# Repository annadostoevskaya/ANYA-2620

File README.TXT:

ANYA-2620 / A2027

Авторы: Kanat M. M. и Anna D. A.
Текущая версия платы: V2I1. Среда разработки: KiCad.

С чего начать

Открыть проект: hardware/v2i1/A2027.kicad_pro
Открыть схему:  hardware/v2i1/A2027.kicad_sch
Открыть плату:  hardware/v2i1/A2027.kicad_pcb
Посмотреть BOM: manufacturing/v2i1/bom/Bill_Of_Materials.csv
Посмотреть CPL: manufacturing/v2i1/cpl/Component_Placement_List.csv

Артикулы производителей, поставщики, ссылки на товары и Datasheet
хранятся в полях компонентов схемы. Для выгрузки BOM в редакторе схемы:
Tools → Generate Bill of Materials… → preset Purchasing BOM →
format Purchasing CSV → Export. Путь вывода уже настроен.
Preset Purchasing BOM - fitted only исключает DNP (C1,C6,C18).
Редактировать закупочные данные через Tools → Edit Symbol Fields…

Структура

hardware/
  v2i1/               Текущие исходники KiCad: проект, схема и плата.
    libs/              Локальная библиотека символов.
    3dmodels/          Локальные 3D-модели.
    .history/          Сохранённая история KiCad; отдельный вложенный Git-репозиторий.

firmware/
  Firmware.ioc         Конфигурация STM32CubeMX. Исходников прошивки пока нет.

manufacturing/
  v2i1/
    gerbers/           Gerber, сверловка и A2027-job.gbrjob в одной папке.
    bom/               Экспортированный BOM текущей платы.
    cpl/               Позиции 81 устанавливаемого компонента; X/Y в mm,
                       верхняя сторона top, поворот в градусах 0–360.
                       Координаты KiCad без сдвига начала; DNP, отверстия
                       и паяная перемычка исключены. Включены 5 THT-разъёмов.

docs/
  design/              Блок-схема Excalidraw и расчёты Mathcad.
  references/          Справочные материалы и схемы отладочных плат.
  reviews/             Отчёты ревью платы.

archive/
  v1i1/source/         Предыдущая версия платы в Altium.
  v1i1/release-template/ Старый шаблон выпуска V1I1 с инструкциями.
  altium/              Старые библиотеки, 3D-модели и правила Altium.
  footprint-expert-2025/ Исходные материалы Footprint Expert.
  project-template/    Исходный README и прежние шаблонные инструкции.
  local-state/         Сохранённые служебные файлы Finder из старых каталогов.

Как поддерживать порядок

Редактировать текущую электронику в hardware/v2i1/.
Файлы *.kicad_pro, *.kicad_sch и *.kicad_pcb оставлять с одним именем A2027.
При изменении версии создавать новые каталоги с номером версии.
Экспортировать Gerber в manufacturing/v2i1/gerbers/, BOM — в manufacturing/v2i1/bom/.
Настройки вывода KiCad обновлены на эти пути. Локальные библиотеки и модели
используют ${KIPRJMOD} и перемещены вместе с проектом.

Gerber — существовавший экспорт от 2026-11-03; при реорганизации
они не пересоздавались. BOM и CPL сгенерированы из текущих исходников.
Перед отправкой в производство
проверять их соответствие текущим исходникам и фиксировать утверждённый выпуск.
Рабочие изменения сохранять в Git основного проекта. Вложенная .history
сохранена как была и не заменяет историю основного репозитория.

Реорганизация каталогов: 2026-11-03. Содержимое прежних файлов сохранено,
кроме настроек путей экспорта KiCad и ссылок на библиотеки старого Altium.

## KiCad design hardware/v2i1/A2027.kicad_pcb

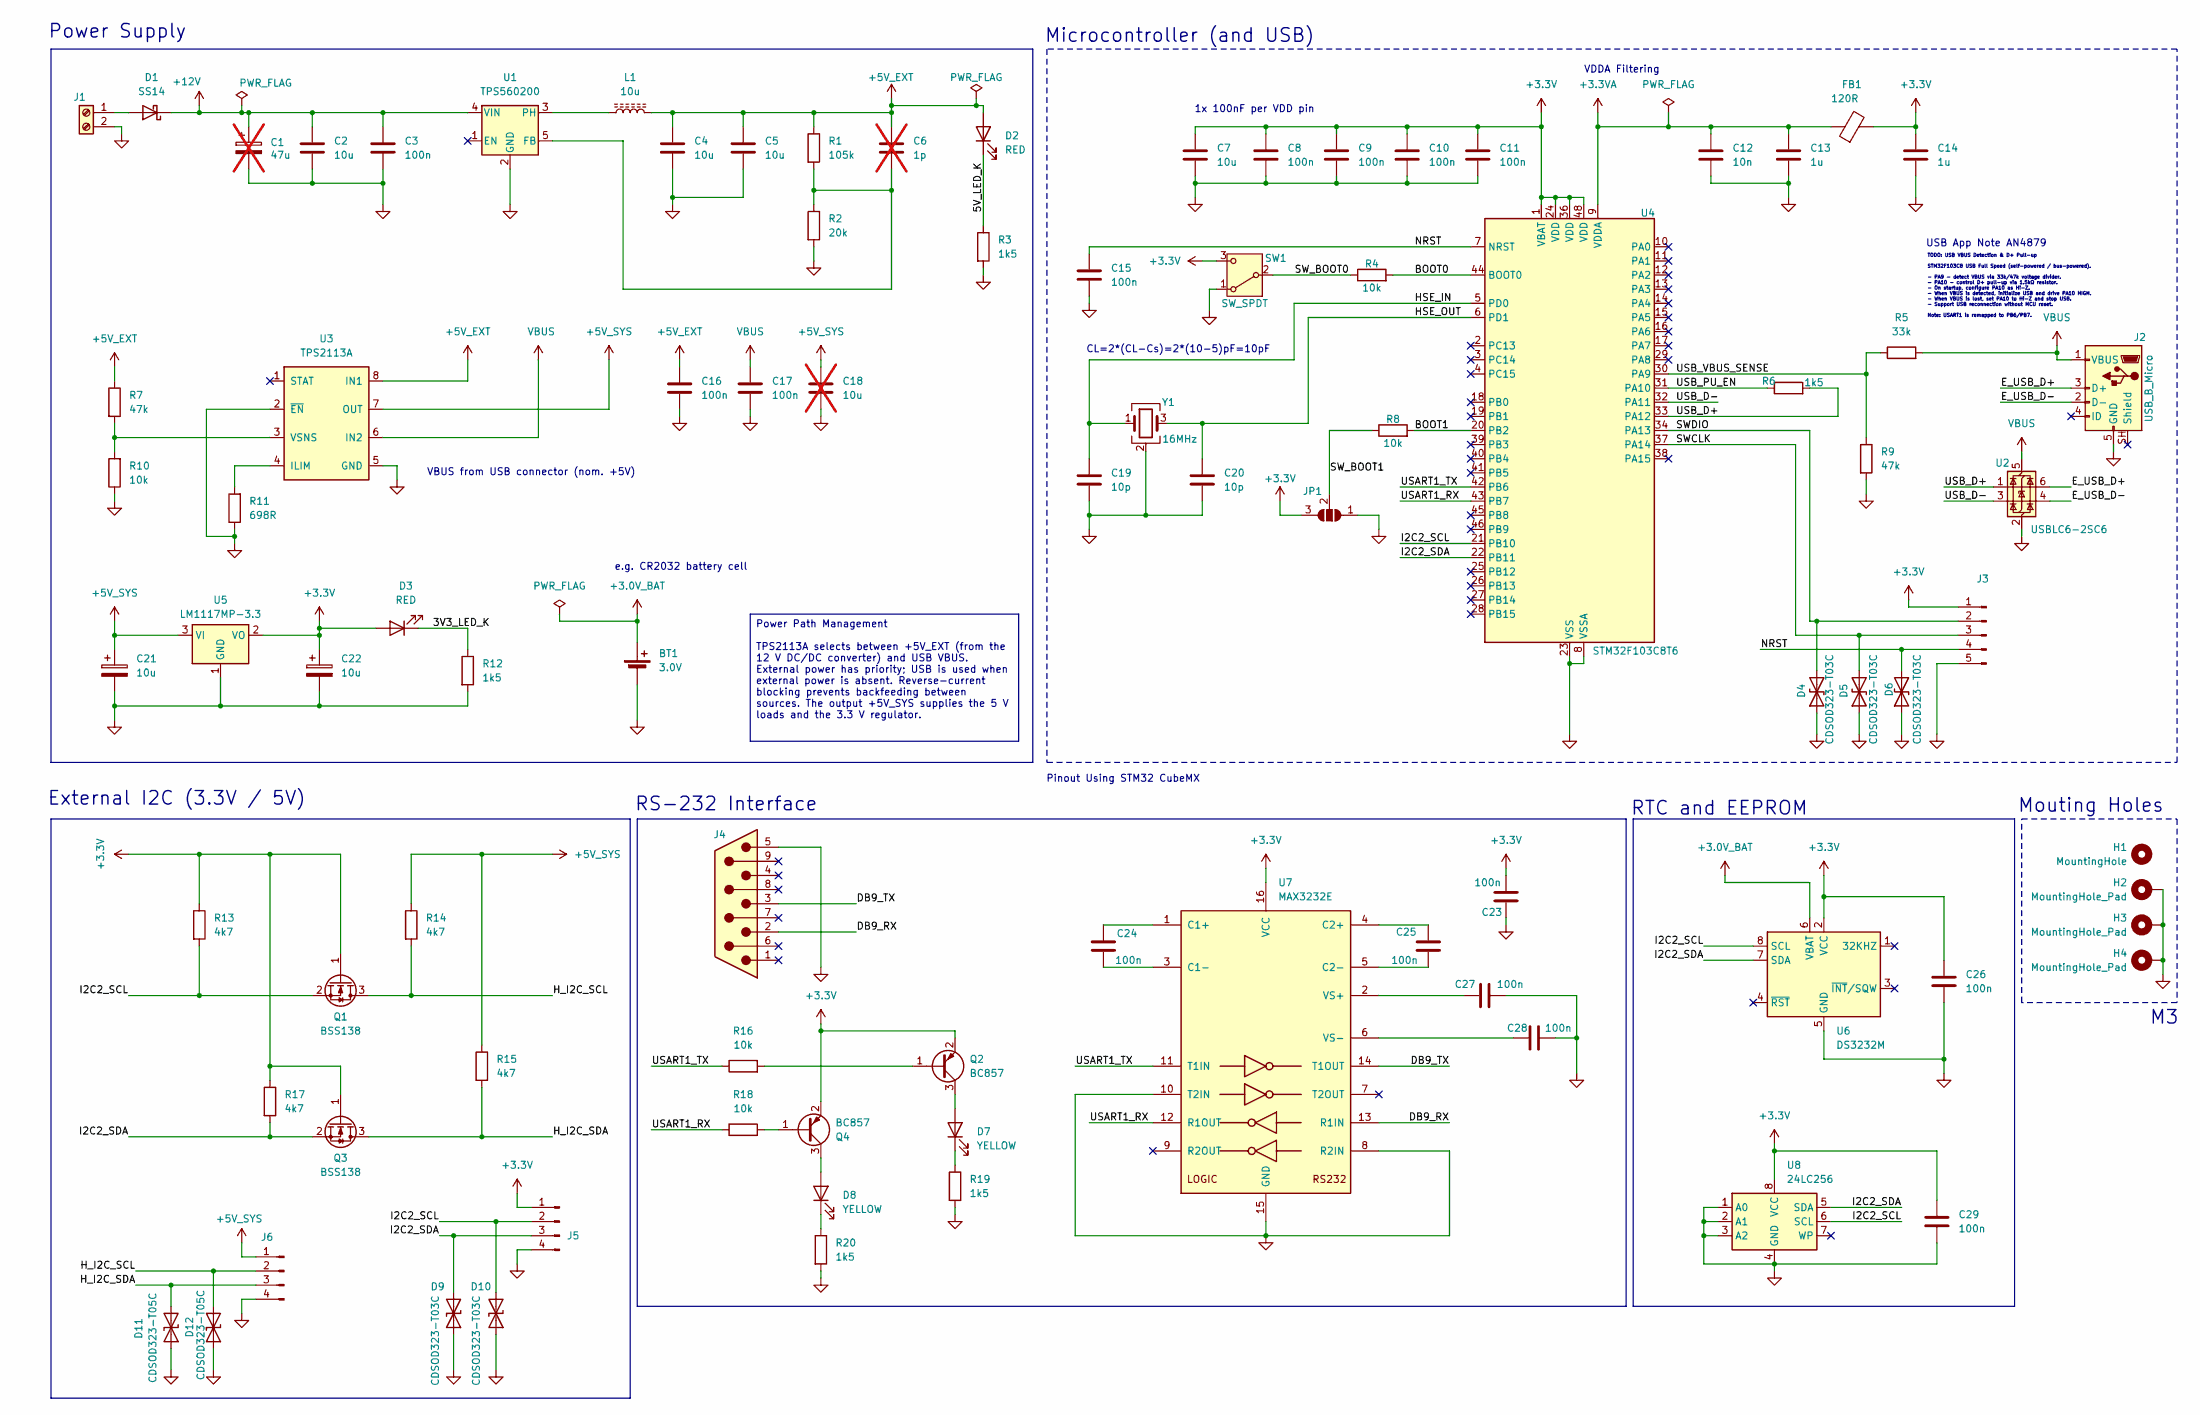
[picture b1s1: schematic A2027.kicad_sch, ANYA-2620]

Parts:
BT1: 3.0V; BatteryHolder_Keystone_3034_1x20mm; Manufacturer_Part_Number 3034
C1: 47u; CP_Elec_6.3x5.8; not fitted
C2, C4, C5: 10u; C_1210_3225Metric; Manufacturer_Part_Number CL32B106KBJNNNE
C3, C8, C9, C10, C11, C15, C16, C17, C23, C24, C25, C26, C27, C28, C29: 100n; C_0402_1005Metric; Manufacturer_Part_Number CL05B104KB5NNNC
C6: 1p; C_0402_1005Metric; not fitted
C7: 10u; C_0603_1608Metric; Manufacturer_Part_Number CL10B106MQ8NRNC
C12: 10n; C_0402_1005Metric; Manufacturer_Part_Number CL05B103KB5NNNC
C13, C14: 1u; C_0402_1005Metric; Manufacturer_Part_Number GRM155R70J105KA12D
C18: 10u; C_0603_1608Metric; not fitted
C19, C20: 10p; C_0402_1005Metric; Manufacturer_Part_Number GRM1555C1H100JA01D
C21, C22: 10u; CP_EIA-3216-18_Kemet-A; Manufacturer_Part_Number TAJA106K016RNJ
D1: SS14; D_SMA; Manufacturer_Part_Number SS14
D2, D3: RED; LED_0603_1608Metric; Manufacturer_Part_Number KT-0603R
D4, D5, D6, D9, D10: CDSOD323-T03C; D_SOD-323; Manufacturer_Part_Number CDSOD323-T03C
D7, D8: YELLOW; LED_0603_1608Metric; Manufacturer_Part_Number KT-0603Y
D11, D12: CDSOD323-T05C; D_SOD-323; Manufacturer_Part_Number CDSOD323-T05C
FB1: 120R; L_0603_1608Metric; Manufacturer_Part_Number BLM18PG121SN1D
H1: MountingHole; MountingHole_3.2mm_M3
H2, H3, H4: MountingHole_Pad; MountingHole_3.2mm_M3_Pad_TopBottom
J1: Screw_Terminal_01x02; TerminalBlock_Phoenix_MKDS-1,5-2-5.08_1x02_P5.08mm_Horizont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; Manufacturer_Part_Number 1715721
J2: USB_B_Micro; USB_Micro-B_Wuerth_629105150521; Manufacturer_Part_Number 629105150521
J3: Conn_01x05_Pin; PinHeader_1x05_P2.54mm_Vertical; Manufacturer_Part_Number PZ254V-11-05P
J4: DS1037-09MNAKT74-0CC; DSUB-9_Pins_Horizontal_P2.77x2.84mm_EdgePinOffset7.70mm_Hou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; Manufacturer_Part_Number DS1037-09MNAKT74-0CC
J5, J6: Conn_01x04_Pin; PinHeader_1x04_P2.54mm_Vertical; Manufacturer_Part_Number PZ254V-11-04P
JP1: SolderJumper_3_Open; SolderJumper-3_P2.0mm_Open_TrianglePad1.0x1.5mm
L1: 10u; L_Bourns_SRP5030T; Manufacturer_Part_Number SRP5030T-100M
Q1, Q3: BSS138; SOT-23; Manufacturer_Part_Number BSS138LT1G
Q2, Q4: BC857; SOT-23; Manufacturer_Part_Number BC857BLT1G
R1: 105k; R_0402_1005Metric; Manufacturer_Part_Number 0402WGF1053TCE
R2: 20k; R_0402_1005Metric; Manufacturer_Part_Number 0402WGF2002TCE
R3, R12, R19, R20: 1k5; R_0402_1005Metric; Manufacturer_Part_Number 0402WGF1501TCE
R4, R8, R10, R16, R18: 10k; R_0402_1005Metric; Manufacturer_Part_Number 0402WGF1002TCE
R5: 33k; R_0402_1005Metric; Manufacturer_Part_Number 0402WGF3302TCE
R6: 1k5; R_0603_1608Metric; Manufacturer_Part_Number 0603WAF1501T5E
R7, R9: 47k; R_0402_1005Metric; Manufacturer_Part_Number 0402WGF4702TCE
R11: 698R; R_0402_1005Metric; Manufacturer_Part_Number 0402WGF6980TCE
R13, R14, R15, R17: 4k7; R_0402_1005Metric; Manufacturer_Part_Number 0402WGF4701TCE
SW1: SW_SPDT; SW_SPDT_PCM12; Manufacturer_Part_Number PCM12SMTR
U1: TPS560200; SOT-23-5; Manufacturer_Part_Number TPS560200DBVR
U2: USBLC6-2SC6; SOT-23-6; Manufacturer_Part_Number USBLC6-2SC6
U3: TPS2113A; TSSOP-8_4.4x3mm_P0.65mm; Manufacturer_Part_Number TPS2113APWR
U4: STM32F103C8T6; LQFP-48_7x7mm_P0.5mm; Manufacturer_Part_Number STM32F103C8T6
U5: LM1117MP-3.3; SOT-223-3_TabPin2; Manufacturer_Part_Number LM1117MP-3.3/NOPB
U6: DS3232M; SOIC-8_3.9x4.9mm_P1.27mm; Manufacturer_Part_Number DS3232MZ+
U7: MAX3232E; TSSOP-16_4.4x5mm_P0.65mm; Manufacturer_Part_Number MAX3232EIPWR
U8: 24LC256; SOIC-8_3.9x4.9mm_P1.27mm; Manufacturer_Part_Number 24LC256T-I/SN
Y1: 16MHz; Crystal_SMD_3225-4Pin_3.2x2.5mm; Manufacturer_Part_Number X322516MMB4SI

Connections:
+3.0V_BAT: BT1.1 (+), U6.6 (VBAT)
+3.3V: C7.1, C8.1, C9.1, C10.1, C11.1, C14.1, C22.1, C23.2, C26.1, C29.1, D3.2 (A), FB1.2, J3.1, J5.1, JP1.3 (B), Q1.1 (G), Q2.2 (E), Q3.1 (G), Q4.2 (E), R13.1, R17.1, SW1.3 (C), U4.1 (VBAT), U4.24 (VDD), U4.36 (VDD), U4.48 (VDD), U5.2 (VO), U6.2 (VCC), U7.16 (VCC), U8.8 (VCC)
+3.3VA: C12.1, C13.1, FB1.1, U4.9 (VDDA)
+5V_EXT: C4.1, C5.1, C6.1, C16.1, D2.2 (A), L1.2, R1.1, R7.1, U3.8 (IN1)
+5V_SYS: C18.1, C21.1, J6.1, R14.1, R15.1, U3.7 (OUT), U5.3 (VI)
+12V: C1.1, C2.1, C3.1, D1.1 (K), U1.4 (VIN)
/3V3_LED_K: D3.1 (K), R12.1
/5V_LED_K: D2.1 (K), R3.1
/BOOT0: R4.2, U4.44 (BOOT0)
/BOOT1: R8.2, U4.20 (PB2)
/DB9_RX: J4.2, U7.13 (R1IN)
/DB9_TX: J4.3, U7.14 (T1OUT)
/E_USB_D+: J2.3 (D+), U2.6 (I/O1)
/E_USB_D-: J2.2 (D-), U2.4 (I/O2)
/HSE_IN: C19.1, U4.5 (PD0), Y1.1
/HSE_OUT: C20.1, U4.6 (PD1), Y1.3
/H_I2C_SCL: D12.2 (A2), J6.2, Q1.3 (D), R14.2
/H_I2C_SDA: D11.2 (A2), J6.3, Q3.3 (D), R15.2
/I2C2_SCL: D10.2 (A2), J5.2, Q1.2 (S), R13.2, U4.21 (PB10), U6.8 (SCL), U8.6 (SCL)
/I2C2_SDA: D9.2 (A2), J5.3, Q3.2 (S), R17.2, U4.22 (PB11), U6.7 (SDA), U8.5 (SDA)
/NRST: C15.1, D6.2 (A2), J3.4, U4.7 (NRST)
/SWCLK: D5.2 (A2), J3.3, U4.37 (PA14)
/SWDIO: D4.2 (A2), J3.2, U4.34 (PA13)
/SW_BOOT0: R4.1, SW1.2 (B)
/SW_BOOT1: JP1.2 (C), R8.1
/USART1_RX: R18.1, U4.43 (PB7), U7.12 (R1OUT)
/USART1_TX: R16.1, U4.42 (PB6), U7.11 (T1IN)
/USB_D+: R6.2, U2.1 (I/O1), U4.33 (PA12)
/USB_D-: U2.3 (I/O2), U4.32 (PA11)
/USB_PU_EN: R6.1, U4.31 (PA10)
/USB_VBUS_SENSE: R5.1, R9.1, U4.30 (PA9)
GND: BT1.2 (-), C1.2, C2.2, C3.2, C4.2, C5.2, C7.2, C8.2, C9.2, C10.2, C11.2, C12.2, C13.2, C14.2, C15.2, C16.2, C17.2, C18.2, C19.2, C20.2, C21.2, C22.2, C23.1, C26.2, C27.2, C28.2, C29.2, D4.1 (A1), D5.1 (A1), D6.1 (A1), D9.1 (A1), D10.1 (A1), D11.1 (A1), D12.1 (A1), H2.1 (1_1), H3.1 (1_1), H4.1 (1_1), J1.2, J2.5 (GND), J3.5, J4.5, J5.4, J6.4, JP1.1 (A), R2.2, R3.2, R9.2, R10.1, R11.1, R12.2, R19.2, R20.2, SW1.1 (A), U1.2 (GND), U2.2 (GND), U3.2 (~EN), U3.5 (GND), U4.8 (VSSA), U4.23 (VSS), U4.35 (VSS), U4.47 (VSS), U5.1 (GND), U6.5 (GND), U7.8 (R2IN), U7.10 (T2IN), U7.15 (GND), U8.1 (A0), U8.2 (A1), U8.3 (A2), U8.4 (GND), Y1.2 (G), Y1.4 (G)
unnamed: D1.2 (A), J1.1
unnamed: D7.2 (A), Q2.3 (C)
unnamed: D7.1 (K), R19.1
unnamed: D8.2 (A), Q4.3 (C)
unnamed: D8.1 (K), R20.1
unnamed: Q2.1 (B), R16.2
unnamed: Q4.1 (B), R18.2
unnamed: C6.2, R1.2, R2.1, U1.5 (FB)
unnamed: L1.1, U1.3 (PH)
unnamed: R11.2, U3.4 (ILIM)
unnamed: R7.2, R10.2, U3.3 (VSNS)
unnamed: C24.1, U7.1 (C1+)
unnamed: C24.2, U7.3 (C1-)
unnamed: C25.1, U7.4 (C2+)
unnamed: C25.2, U7.5 (C2-)
unnamed: C27.1, U7.2 (VS+)
unnamed: C28.1, U7.6 (VS-)
VBUS: C17.1, J2.1 (VBUS), R5.2, U2.5 (VBUS), U3.6 (IN2)

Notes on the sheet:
TODO: USB VBUS Detection & D+ Pull-up STM32F103C8 USB Full Speed (self-powered / bus-powered). - PA9 - detect VBUS via 33k/47k voltage divider. - PA10 - control D+ pull-up via 1.5kΩ resistor. - On startup, configure PA10 as Hi-Z. - When VBUS is detected, initialize USB and drive PA10 HIGH. - When V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
RTC and EEPROM
Mouting Holes
Power Supply
External I2C (3.3V / 5V)
VBUS from USB connector (nom. +5V)
VDDA Filtering
RS-232 Interface
Microcontroller (and USB)
CL=2*(CL-Cs)=2*(10-5)pF=10pF
Pinout Using STM32 CubeMX
USB App Note AN4879
1x 100nF per VDD pin
e.g. CR2032 battery cell
Power Path Management TPS2113A selects between +5V_EXT (from the 12 V DC/DC converter) and USB VBUS. External power has priority; USB is used when external power is absent. Reverse-current blocking prevents backfeeding between sources. The output +5V_SYS supplies the 5 V loads and the 3.3 V regulat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

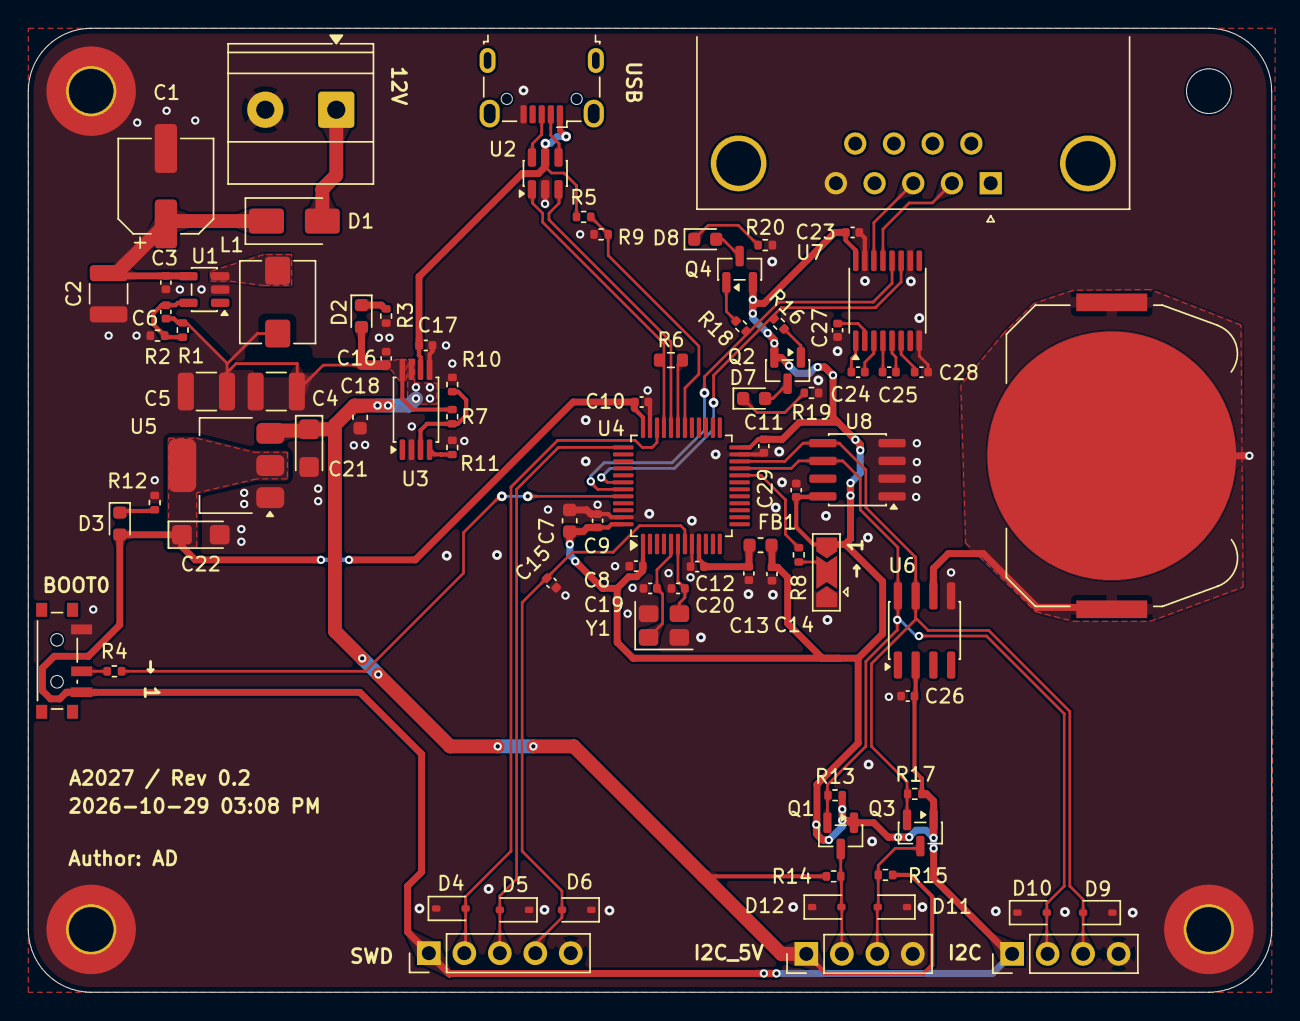
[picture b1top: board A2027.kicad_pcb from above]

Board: 2 copper layers, 89.0 x 69.0 mm, 89 parts (0 on the bottom side), 50 nets.

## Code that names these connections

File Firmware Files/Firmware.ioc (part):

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Mcu.Name=STM32F103C(8-B)Tx
Mcu.Package=LQFP48
Mcu.UserName=STM32F103C8Tx
PA10.Signal=GPIO_Input
PA11.Mode=Device
PA11.Signal=USB_DM
PA12.Mode=Device
PA12.Signal=USB_DP
PA13.Mode=Serial_Wire
PA13.Signal=SYS_JTMS-SWDIO
PA14.Mode=Serial_Wire
PA14.Signal=SYS_JTCK-SWCLK
PA9.Signal=GPIO_Input
PB10.Mode=I2C
PB10.Signal=I2C2_SCL
PB11.Mode=I2C
PB11.Signal=I2C2_SDA
PB2.Signal=GPIO_Output
PB6.Mode=Asynchronous
PB6.Signal=USART1_TX
PB7.Mode=Asynchronous
PB7.Signal=USART1_RX
PD0-OSC_IN.Mode=HSE-External-Oscillator
PD0-OSC_IN.Signal=RCC_OSC_IN
PD1-OSC_OUT.Mode=HSE-External-Oscillator
PD1-OSC_OUT.Signal=RCC_OSC_OUT
RCC.HSE_VALUE=16000000
RCC.SYSCLKFreq_VALUE=16000000
RCC.SYSCLKSource=RCC_SYSCLKSOURCE_HSE
board=custom

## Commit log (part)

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2026-03-29 master :: Block Diagram
2026-03-29 master :: update REAME.TXT
2026-03-30 master :: Altium Project
2026-03-30 master :: Library
2026-03-30 master :: Development Files
2026-03-30 master :: Release Files
2026-03-30 master :: COVER PAGE
2026-03-30 master :: LCD
2026-03-30 master :: update diag, update step file lcd-i2c
2026-03-31 master :: STM32H503RBT6
2026-04-02 master :: lcd, header
2026-04-02 master :: rename
2026-04-02 lcd i2c conn
2026-04-03 master :: connectors, lcd
2026-04-04 master :: power, rtc and fram
2026-04-14 master :: finished all major components and start passives
2026-04-15 master :: passive
2026-05-04 master :: library loader probe
